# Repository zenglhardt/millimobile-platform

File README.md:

**MilliMobile Hardware Platform**

This repo contains the KiCad PCB design files for the development board verison of the MilliMobile. For more information on the platform, see the [project page](https://millimobile.cs.washington.edu/)

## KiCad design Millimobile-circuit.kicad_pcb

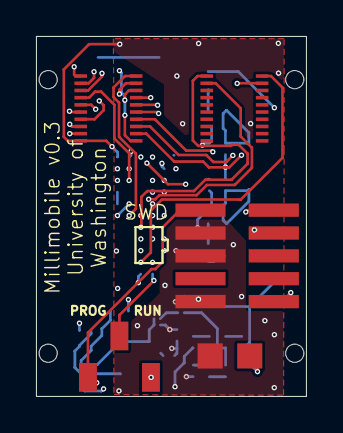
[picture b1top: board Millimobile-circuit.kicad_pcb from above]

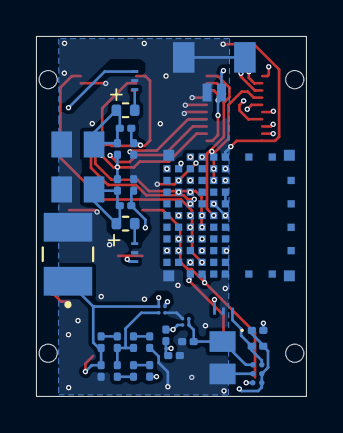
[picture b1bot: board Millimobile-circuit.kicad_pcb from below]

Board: 4 copper layers, 15.0 x 20.0 mm, 38 parts (33 on the bottom side), 49 nets.

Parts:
1.9V1, 2.5V1: TCR3UG10A
1uF1: C_Small; C_0201_0603Metric
C1: 11m; CAPCP3225X100N
C2, C4, C5: 100u; CAPC2012X140N
C7: 330u; CAP_ETPS330MUD
CR1, CR2, CR3: SMS7630-079LF; D_0201_0603Metric
Csmall1: 1u; C_0201_0603Metric
J1: SM02B-SURS-TF(LF)(SN); JST_SM02B-SURS-TF(LF)(SN)
J2, J4: DF40C_2.0_-20DS-0.4V_51_; DF40C2020DS04V51
J3: FTSH-105-01-F-DV-P-TR; SAMTEC_FTSH-105-01-F-DV-P-TR
M1, M2: Motor_DC; R_0402_1005Metric
R1, R2: 3M; R_0201_0603Metric
R3: 2.49M; R_0201_0603Metric
R4: 200K; R_0201_0603Metric
R5: 1M; R_0201_0603Metric
R6, R7, R8: 10M; R_0201_0603Metric
R13, R15, R17, R18: 750K; R_0201_0603Metric
R14, R16: 150K; R_0201_0603Metric
S1: CAS-120A1; CAS120A1
U1: SN74LVC1G3157YZP; SN74LVC1G3157YZPR
U3, U4, U5: CSD17585F5T
U6: ISP2053-AX-RS; LGA72_ISP2053_ISP

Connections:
1.9V: 1.9V1.A2 (VOUT), J2.17, R8.1, S1.3 (NC)
A3: J2.1, U6.B6 (P0.07/AIN3)
A4: J2.3, U6.F10 (P0.25/AIN4)
A5: J2.5, U6.E10 (P0.26/AIN5)
A6: J2.7, U6.E9 (P0.27/AIN6)
A7: J2.2, U6.E6 (P0.28/AIN7)
BATTERY_IN: CR1.1, J2.18, R5.2, U1.B2 (Vcc), U1.C2 (A)
GND: 1.9V1.B2 (GND), 1uF1.2, 2.5V1.B2 (GND), C1.2, C2.2, C4.1, C5.1, C7.2, Csmall1.1, J1.2, J1.S1 (SHIELD), J1.S2 (SHIELD), J2.19, J3.03, J3.05, J3.09, R4.2, R14.2, R16.2, R18.1, U1.B1 (GND), U3.2 (S), U4.2 (S), U5.2 (S), U6.A1 (VSS), U6.A11 (VSS), U6.E7 (VSS), U6.F1 (VSS), U6.F6 (VSS), U6.F9 (VSS), U6.F11 (VSS)
In1: U4.1 (G), U6.D1 (P1.13)
In2: U5.1 (G), U6.D3 (P0.21)
MCU_VDD: S1.2 (COM), U6.C1 (VDD)
Mcap_1: C4.2, CR2.1, M1.1 (+), R13.1
Mcap_1_sense: R13.2, R14.1, U6.B8 (P0.05/AIN1)
Mcap_2: C5.2, CR3.1, M2.1 (+), R15.1
Mcap_2_sense: R15.2, R16.1, U6.B3 (P0.06/AIN2)
Motor_V: CR2.2, CR3.2, U1.C1 (B1)
unnamed: 1.9V1.B1 (CONTROL), R2.2, R3.1, R6.2
unnamed: M1.2 (-), U4.3 (D)
unnamed: M2.2 (-), U5.3 (D)
unnamed: R1.2, R2.1
unnamed: R3.2, R4.1
unnamed: R6.1, R7.2
unnamed: R7.1, R8.2
unnamed: R5.1, U1.A2 (S), U3.3 (D)
unnamed: U6.F7 (OUT_ANT), U6.F8 (OUT_MOD)
PROG_VDD: J3.01, S1.1 (NO)
QSPI0: J2.14, U6.C2 (P0.13/QSPI0)
QSPI1: J2.12, U6.C5 (P0.14/QSPI1)
QSPI2: J2.8, U6.C4 (P0.15/QSPI2)
QSPI3: J2.6, U6.C6 (P0.16/QSPI3)
QSPI_CLK: J2.4, U6.C9 (P0.17/QSPI_CLK)
QSPI_CS: J2.16, U6.D4 (P0.18/QSPI_CS)
SCL: J2.9, U6.B10 (P1.02/I2C)
SDA: J2.10, U6.A3 (P1.03/I2C)
SPI_CSN: J4.4, U6.C8 (P0.11/TD0)
SPI_DCX: J4.2, U6.D2 (P0.12/TC)
SPI_MISO: J2.11, U6.A10 (P0.10/TD1)
SPI_MOSI: J2.15, U6.C7 (P0.09/TD2)
SPI_SCK: J2.13, U6.B9 (P0.08/TD3)
SWDCLK: J3.04, U6.D11 (SWDCLK)
SWDIO: J3.02, U6.C11 (SWDIO)
Solar_In: CR1.2, J1.1, J2.20
SuperCap: 1.9V1.A1 (VIN), 1uF1.1, 2.5V1.A2 (VOUT), C1.1, C7.1, R1.1, R17.1
SuperCap_sense: R17.2, R18.2, U6.B4 (P0.04/AIN0)
Switch_CTRL: U3.1 (G), U6.F3 (P0.23)
Sys_V: 2.5V1.A1 (VIN), 2.5V1.B1 (CONTROL), C2.1, Csmall1.2, U1.A1 (B2)
UART_RXD: J4.1, U6.D5 (P0.22)
UART_TXD: J4.3, U6.D6 (P0.20)
nRST: J3.10, U6.E11 (NRST)

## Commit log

2024-04-09 initial V0.3 Commit
2024-06-07 capacitor part change
2024-06-07 updated cap parts in BOM
